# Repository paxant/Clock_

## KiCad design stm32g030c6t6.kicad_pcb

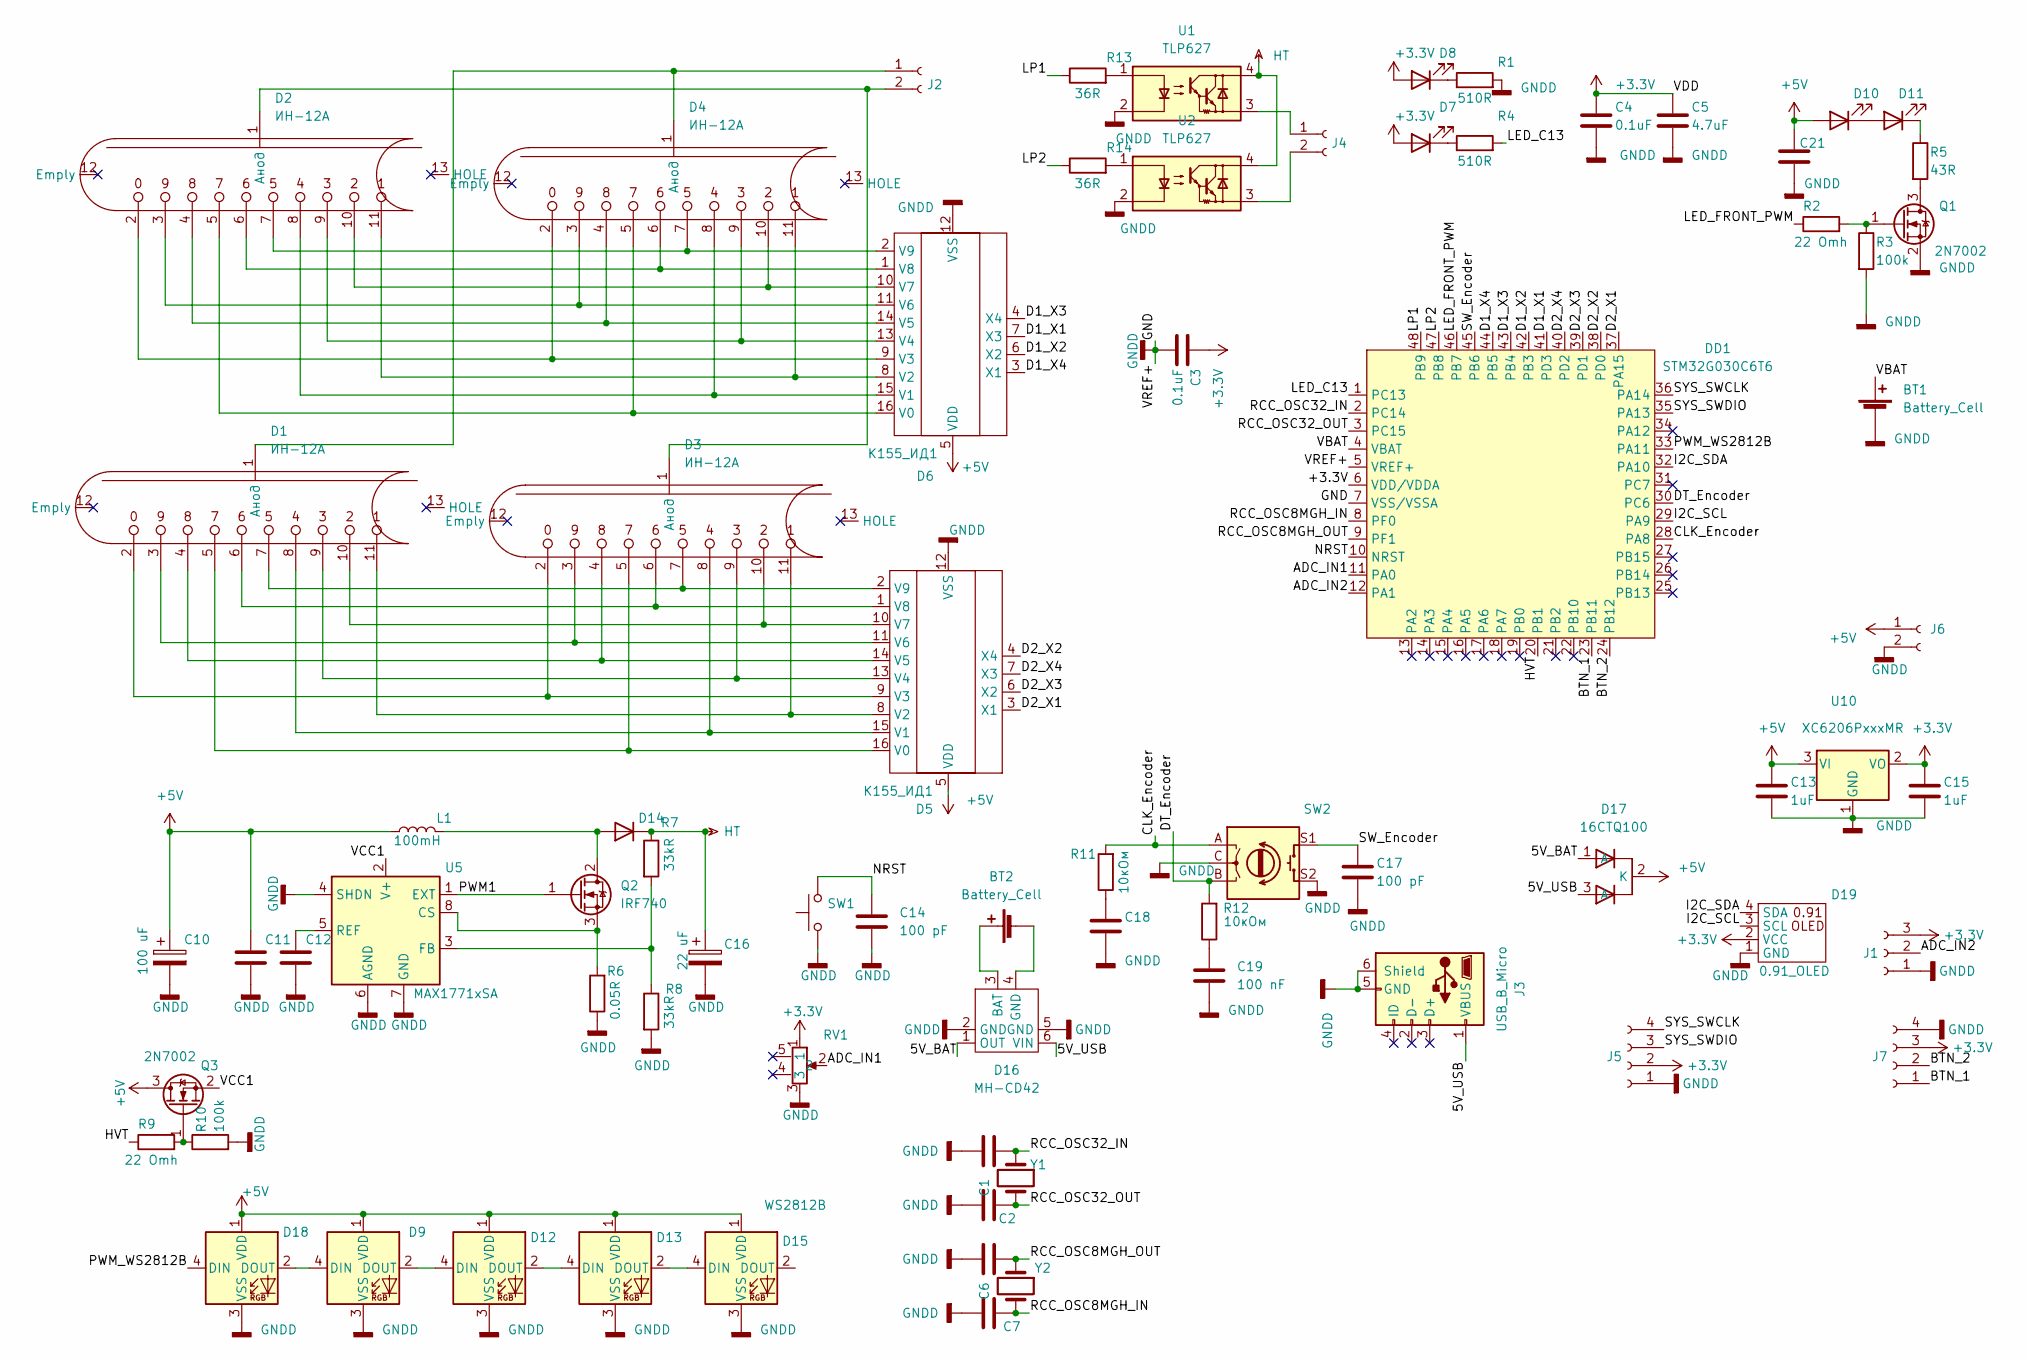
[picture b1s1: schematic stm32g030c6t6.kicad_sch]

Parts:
BT1: Battery_Cell; BAT
BT2: Battery_Cell; PinHeader_1x02_P2.54mm_Vertical
C1, C2, C6, C7: C_0805_2012Metric
C3, C4: 0.1uF; C_1206_3216Metric
C5: 4.7uF; C_1206_3216Metric
C10: 100 uF; CP_Radial_Tantal_D5.0mm_P2.50mm
C11, C12, C18, C21: C_1206_3216Metric
C13, C15: 1uF; C_1206_3216Metric
C14, C17: 100 pF; C_1206_3216Metric
C16: 22 uF; CP_Radial_D8.0mm_P3.50mm
C19: 100 nF; C_1206_3216Metric
D1, D2, D3, D4: ИН-12А; ИН12А
D5, D6: К155_ИД1; К155ИД1
D7, D8: LED_0603_1608Metric
D9, D12, D13, D18: LED_WS2812B_PLCC4_5.0x5.0mm_P3.2mm
D10, D11: LED_D3.0mm
D14: D_DO-41_SOD81_P12.70mm_Horizontal
D15: WS2812B; LED_WS2812B_PLCC4_5.0x5.0mm_P3.2mm
D16: MH-CD42; MH
D17: 16CTQ100; TO-263-2
D19: 0.91_OLED; 0.91OLED
DD1: STM32G030C6T6; LQFP-48_7x7mm_P0.5mm
J1: PinSocket_1x03_P2.54mm_Vertical
J2, J4, J6: PinHeader_1x02_P2.54mm_Vertical
J3: USB_B_Micro; USB_Micro-B_Amphenol_10104110_Horizontal
J5, J7: PinHeader_1x04_P2.54mm_Vertical
L1: 100mH; L_Radial_D9.5mm_P5.00mm_Fastron_07HVP
Q1, Q3: 2N7002; SOT-23
Q2: IRF740; TO-263-2
R1, R4: 510R; R_1206_3216Metric
R2, R9: 22 Omh; R_1206_3216Metric
R3, R10: 100k; R_1206_3216Metric
R5: 43R; R_1206_3216Metric
R6: 0.05R; R_Axial_DIN0309_L9.0mm_D3.2mm_P15.24mm_Horizontal
R7, R8: 33kR; R_Axial_DIN0309_L9.0mm_D3.2mm_P15.24mm_Horizontal
R11, R12: 10кОм; R_1206_3216Metric
R13, R14: 36R; R_1206_3216Metric
RV1: res
SW1: SW_SPST_FSMSM
SW2: RotaryEncoder_Alps_EC12E-Switch_Vertical_H20mm
U1, U2: TLP627; DIP-4_W7.62mm
U5: MAX1771xSA; SO-8_3.9x4.9mm_P1.27mm
U10: XC6206PxxxMR; SOT-23-3
Y1: Crystal_C26-LF_D2.1mm_L6.5mm_Horizontal
Y2: Crystal_SMD_HC49-SD

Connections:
+3.3V: C3.1, C4.1, C5.1, C15.1, D7.2 (A), D8.2 (A), D19.2 (VCC), DD1.6 (VDD/VDDA), J1.3, J5.2, J7.3, RV1.1, U10.2 (VO)
+5V: C10.1, C11.1, C13.1, C21.2, D5.5 (VDD), D6.5 (VDD), D9.1 (VDD), D10.2 (A), D12.1 (VDD), D13.1 (VDD), D15.1 (VDD), D17.2 (K), D18.1 (VDD), J6.1, L1.1, Q3.3 (D), U10.3 (VI)
/5V_BAT: D16.1 (OUT), D17.1 (A)
/5V_USB: D16.6 (VIN), D17.3 (A), J3.1 (VBUS)
/ADC_IN1: DD1.11 (PA0), RV1.2
/ADC_IN2: DD1.12 (PA1), J1.2
/BTN_1: DD1.23 (PB11), J7.1
/BTN_2: DD1.24 (PB12), J7.2
/CLK_Encoder: DD1.28 (PA8), R11.2, SW2.A
/D1_X1: D6.7 (X3), DD1.41 (PD3)
/D1_X2: D6.6 (X2), DD1.42 (PB3)
/D1_X3: D6.4 (X4), DD1.43 (PB4)
/D1_X4: D6.3 (X1), DD1.44 (PB5)
/D2_X1: D5.3 (X1), DD1.37 (PA15)
/D2_X2: D5.4 (X4), DD1.38 (PD0)
/D2_X3: D5.6 (X2), DD1.39 (PD1)
/D2_X4: D5.7 (X3), DD1.40 (PD2)
/DT_Encoder: DD1.30 (PC6), R12.2, SW2.B
/HVT: DD1.20 (PB1), R9.1
/I2C_SCL: D19.3 (SCL), DD1.29 (PA9)
/I2C_SDA: D19.4 (SDA), DD1.32 (PA10)
/LED_C13: DD1.1 (PC13), R4.2
/LED_FRONT_PWM: DD1.46 (PB7), R2.1
/LP1: DD1.48 (PB9), R13.1
/LP2: DD1.47 (PB8), R14.1
/NRST: C14.1, DD1.10 (NRST), SW1.2
/PWM1: Q2.1 (G), U5.1 (EXT)
/PWM_WS2812B: D18.4 (DIN), DD1.33 (PA11)
/RCC_OSC8MGH_IN: C7.1, DD1.8 (PF0), Y2.2
/RCC_OSC8MGH_OUT: C6.1, DD1.9 (PF1), Y2.1
/RCC_OSC32_IN: C1.1, DD1.2 (PC14), Y1.1
/RCC_OSC32_OUT: C2.1, DD1.3 (PC15), Y1.2
/SW_Encoder: C17.1, DD1.45 (PB6), SW2.S1
/SYS_SWCLK: DD1.36 (PA14), J5.4
/SYS_SWDIO: DD1.35 (PA13), J5.3
/VBAT: BT1.1 (+), DD1.4 (VBAT)
/VCC1: Q3.2 (S), U5.2 (V+)
GNDD: BT1.2 (-), C1.2, C2.2, C3.2, C4.2, C5.2, C6.2, C7.2, C10.2, C11.2, C12.2, C13.2, C14.2, C15.2, C16.2, C17.2, C18.2, C19.2, C21.1, D5.12 (VSS), D6.12 (VSS), D9.3 (VSS), D12.3 (VSS), D13.3 (VSS), D15.3 (VSS), D16.2 (GND), D16.5 (GND), D18.3 (VSS), D19.1 (GND), DD1.5 (VREF+), DD1.7 (VSS/VSSA), J1.1, J3.5 (GND), J3.6 (Shield), J5.1, J6.2, J7.4, Q1.2 (S), R1.2, R3.2, R6.1, R8.2, R10.2, RV1.3, SW1.1, SW2.C, SW2.S2, U1.2, U2.2, U5.4 (SHDN), U5.6 (AGND), U5.7 (GND), U10.1 (GND)
HT: C16.1, D14.2 (K), R7.1, U1.4, U2.4
unnamed: BT2.1 (+), D16.3 (BAT)
unnamed: BT2.2 (-), D16.4 (GND)
unnamed: C12.1, U5.5 (REF)
unnamed: C18.1, R11.1
unnamed: C19.1, R12.1
unnamed: D1.1 (Анод), D4.1 (Анод), J2.1
unnamed: D2.4, D4.4, D6.14 (V5)
unnamed: D2.5, D4.5, D6.16 (V0)
unnamed: D2.8, D4.8, D6.15 (V1)
unnamed: D2.9, D4.9, D6.13 (V4)
unnamed: D2.10, D4.10, D6.10 (V7)
unnamed: D2.1 (Анод), D3.1 (Анод), J2.2
unnamed: D2.3, D4.3, D6.11 (V6)
unnamed: D1.6, D3.6, D5.1 (V8)
unnamed: D1.7, D3.7, D5.2 (V9)
unnamed: D1.11, D3.11, D5.8 (V2)
unnamed: D1.2, D3.2, D5.9 (V3)
unnamed: D1.10, D3.10, D5.10 (V7)
unnamed: D1.3, D3.3, D5.11 (V6)
unnamed: D1.9, D3.9, D5.13 (V4)
unnamed: D1.4, D3.4, D5.14 (V5)
unnamed: D1.8, D3.8, D5.15 (V1)
unnamed: D1.5, D3.5, D5.16 (V0)
unnamed: D2.6, D4.6, D6.1 (V8)
unnamed: D2.7, D4.7, D6.2 (V9)
unnamed: D2.11, D4.11, D6.8 (V2)
unnamed: D2.2, D4.2, D6.9 (V3)
unnamed: D7.1 (K), R4.1
unnamed: D8.1 (K), R1.1
unnamed: D10.1 (K), D11.2 (A)
unnamed: D11.1 (K), R5.1
unnamed: D12.2 (DOUT), D13.4 (DIN)
unnamed: D9.2 (DOUT), D12.4 (DIN)
unnamed: D13.2 (DOUT), D15.4 (DIN)
unnamed: D14.1 (A), L1.2, Q2.2 (D)
unnamed: D9.4 (DIN), D18.2 (DOUT)
unnamed: J4.1, U1.3
unnamed: J4.2, U2.3
unnamed: Q1.1 (G), R2.2, R3.1
unnamed: Q1.3 (D), R5.2
unnamed: Q2.3 (S), R6.2, U5.8 (CS)
unnamed: Q3.1 (G), R9.2, R10.1
unnamed: R7.2, R8.1, U5.3 (FB)
unnamed: R13.2, U1.1
unnamed: R14.2, U2.1

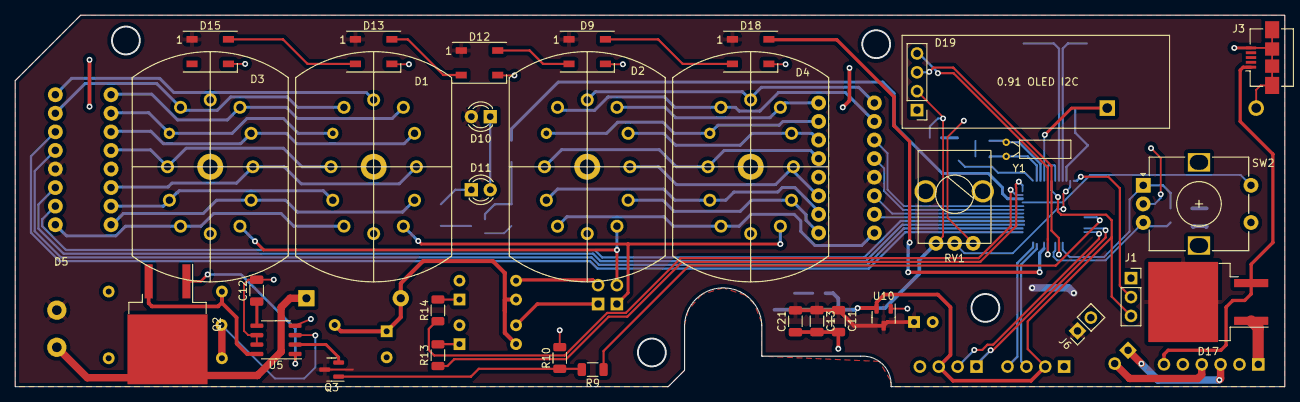
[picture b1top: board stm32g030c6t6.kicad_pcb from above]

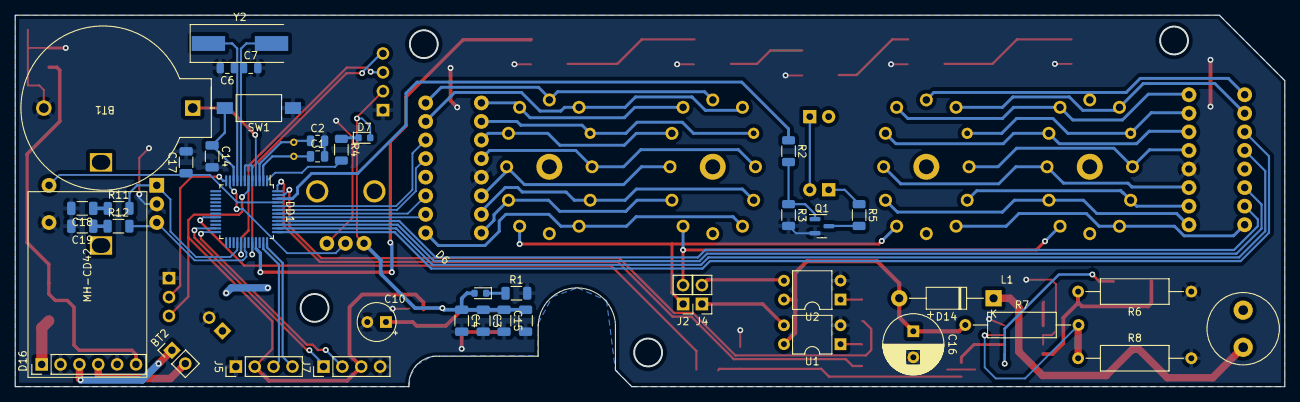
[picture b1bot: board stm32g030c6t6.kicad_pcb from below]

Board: 2 copper layers, 170.9 x 50.0 mm, 74 parts (42 on the bottom side), 84 nets.
